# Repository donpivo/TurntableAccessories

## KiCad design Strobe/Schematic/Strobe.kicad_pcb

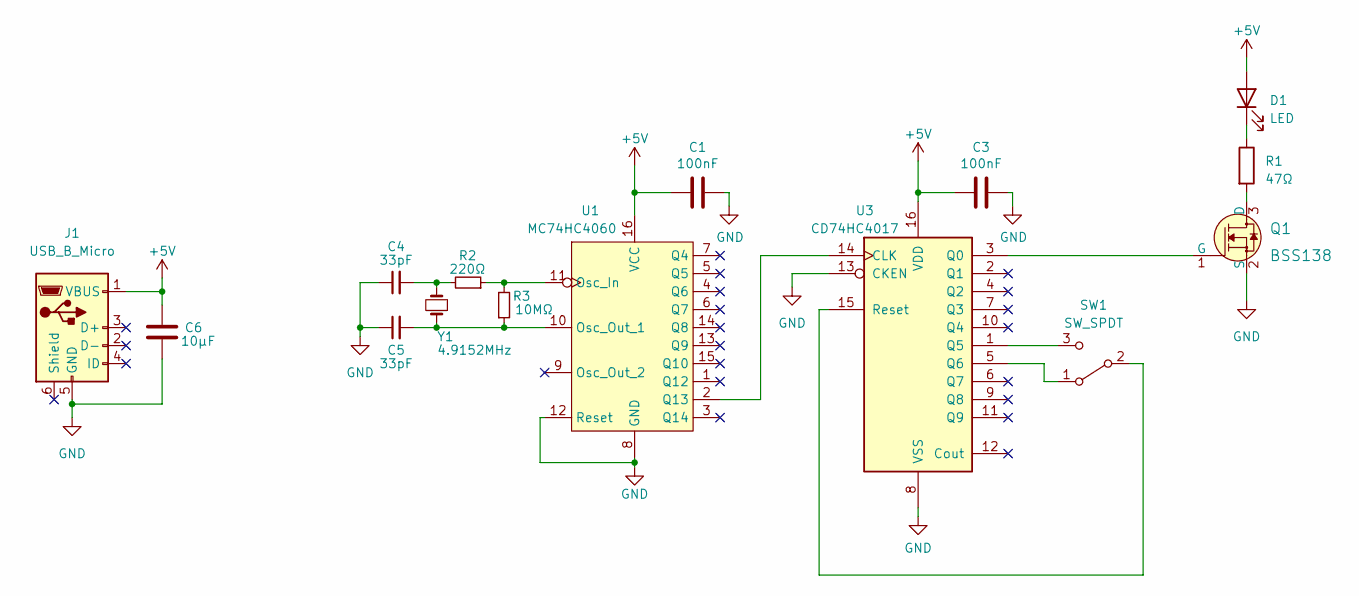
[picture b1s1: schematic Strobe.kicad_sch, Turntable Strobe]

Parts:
C1, C3: 100nF; C_0603_1608Metric_Pad1.08x0.95mm_HandSolder
C4, C5: 33pF; C_0603_1608Metric_Pad1.08x0.95mm_HandSolder
C6: 10µF; C_0603_1608Metric_Pad1.08x0.95mm_HandSolder
D1: LED; LED_D5.0mm
J1: USB_B_Micro; USB_Micro_B_Female_10118194-0001LF
Q1: BSS138; SOT-23-3; MPN BSS138; Digi-Key_PN BSS138CT-ND
R1: 47Ω; R_0603_1608Metric_Pad0.98x0.95mm_HandSolder
R2: 220Ω; R_0603_1608Metric_Pad0.98x0.95mm_HandSolder
R3: 10MΩ; R_0603_1608Metric_Pad0.98x0.95mm_HandSolder
SW1: SW_SPDT; Slide_switch_THT_SPDT
U1: MC74HC4060; TSSOP-16_4.4x5mm_P0.65mm
U3: CD74HC4017; TSSOP-16_4.4x5mm_P0.65mm
Y1: 4.9152MHz; Crystal_HC49-U_Vertical

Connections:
+5V: C1.2, C3.2, C6.2, D1.2 (A), J1.1 (VBUS), U1.16 (VCC), U3.16 (VDD)
GND: C1.1, C3.1, C4.1, C5.1, C6.1, J1.5 (GND), Q1.2 (S), U1.8 (GND), U1.12 (Reset), U3.8 (VSS), U3.13 (CKEN)
unnamed: C4.2, R2.2, Y1.2
unnamed: D1.1 (K), R1.1
unnamed: Q1.3 (D), R1.2
unnamed: Q1.1 (G), U3.3 (Q0)
unnamed: SW1.1 (A), U3.5 (Q6)
unnamed: SW1.2 (B), U3.15 (Reset)
unnamed: SW1.3 (C), U3.1 (Q5)
unnamed: R2.1, R3.2, U1.11 (Osc_In)
unnamed: C5.2, R3.1, U1.10 (Osc_Out_1), Y1.1
unnamed: U1.2 (Q13), U3.14 (CLK)

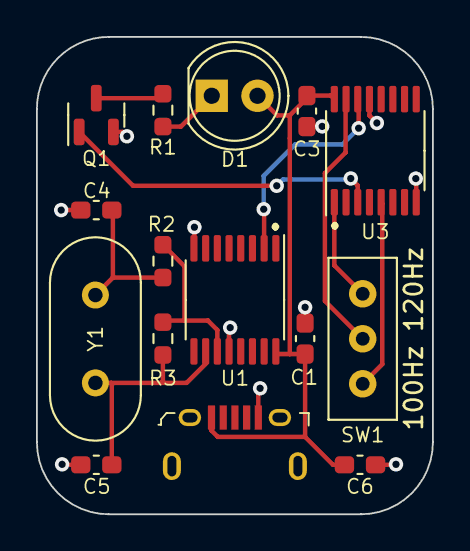
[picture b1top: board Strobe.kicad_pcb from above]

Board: 2 copper layers, 22.0 x 26.5 mm, 15 parts (0 on the bottom side), 12 nets.

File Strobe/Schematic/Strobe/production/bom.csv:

Designator,Footprint,Quantity,Value,LCSC Part #
"C1, C3",0603,2,100nF,
"C4, C5",0603,2,33pF,
C6,0603,1,10µF,
D1,LED_D5.0mm,1,LED,
J1,USB_Micro_B_Female_10118194-0001LF,1,USB_B_Micro,
Q1,SOT-23,1,BSS138,BSS138
R1,0603,1,47Ω,
R2,0603,1,220Ω,
R3,0603,1,10MΩ,
SW1,Slide_switch_THT_SPDT,1,SW_SPDT,
U1,TSSOP-16_4.4x5mm_P0.65mm,1,MC74HC4060,
U3,TSSOP-16_4.4x5mm_P0.65mm,1,CD74HC4017,
Y1,Crystal_HC49-U_Vertical,1,4.9152MHz,

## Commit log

2023-06-02 File cleanup
